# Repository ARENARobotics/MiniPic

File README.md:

# MiniPic: Benchtop Vacuum Tweezers

[-008000?style=for-the-badge&logo=shopify&logoColor=white)](https://arenarobotics.store/products/minipic?variant=54529778090197&utm_source=github&utm_medium=readme&utm_campaign=minipic_repo&utm_content=assembled_badge)
[-0000FF?style=for-the-badge&logo=shopify&logoColor=white)](https://arenarobotics.store/products/minipic?variant=54529778122965&utm_source=github&utm_medium=readme&utm_campaign=minipic_repo&utm_content=kit_badge)

Open-source vacuum tweezers built for repairability. Engineered for SMD soldering and precision rework, with a robust design adaptable to any application requiring controlled suction and handling of small parts.

---

### Features

* **Two operating modes:** foot pedal starts or stops the vacuum motor
* **Solenoid valve** for instant component release
* **Heat-resistant pen** rated up to **160°C**
* **Full set of precision needles and suction cups** for all sizes of SMD components
* Handles components down to **0201 (0.6 x 0.3mm)** and up to **100g**
* **Flexible silicone** vacuum tubing
* **MX hot-swap mechanical switch** in the foot pedal
* **Slip-resistant** rubber feet
* **Inline filter** to protect the vacuum motor
* **LED status indicator** for vacuum engagement

---

### Documentation & Source Files

* **[Assembly Manual](./docs/ASSEMBLY_MANUAL.pdf)** - Step-by-step kit assembly Instructions & quickstart guide
* **[BOM](./BOM.csv)** - Bill of materials including reference links for purchase
* **[Electronics Source](./electronics)** - KiCAD projects for PCBs
* **[CAD Exports](./cad/exports)** - CAD export files (step)
* **[CAD Source](./cad/source%20files)** - CAD source files (FreeCAD)

---

### Our Story

Last summer, we founded a company developing advanced electronics for robot combat competitions. We were inexperienced and didn’t understand the market so the project didn’t work out. Throughout the project, we spent a lot of time designing and assembling PCBs on a tight budget. Like many others, we found that tweezers were cumbersome tools for placing SMD components. The search for a better alternative led us to vacuum tweezers, tools designed to pick and place SMD components using controlled suction. The plan was to buy something off the shelf, but all of the products that were in our price range were not usable. On the other hand, the existing professional tools would have drained our bank account. We were stuck between cheap, low quality options and expensive industrial tools, most of which lacked all the features we were actually looking for.

Out of this frustration, one of our team members got to work, and in a few days, we had a functional tool that made assembly faster and easier than before. After using it ourselves, we realized we could provide a better alternative to others facing the same lack of options. Using our prototype as inspiration, we redesigned our vacuum tweezers from the ground up. Highly functional while still remaining simple and repairable.

See MiniPic in action at: [arenarobotics.store](https://arenarobotics.store?utm_source=github&utm_medium=readme&utm_campaign=minipic_repo&utm_content=story_link).

---

### Licensing

* **Hardware & CAD files (`/electronics`, `/cad`):** Licensed under [CERN-OHL-S-v2](LICENSE.md).
* **Documentation & Media (`/docs`):** Licensed under [CC BY-NC-ND 4.0](https://creativecommons.org/licenses/by-nc-nd/4.0/).
* **Branding & Trademarks:** "MiniPic" and "ARENA Robotics" are trademarks of ARENA Robotics LLC. All rights reserved.

--- 

*Designed & Built by ARENA Robotics.*

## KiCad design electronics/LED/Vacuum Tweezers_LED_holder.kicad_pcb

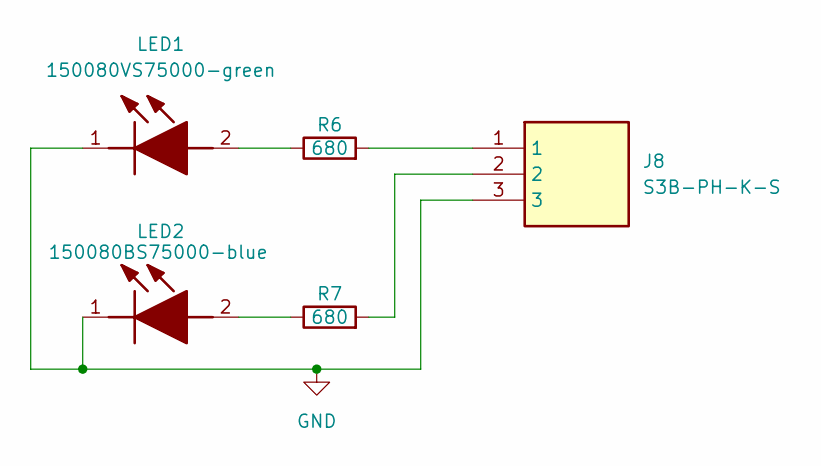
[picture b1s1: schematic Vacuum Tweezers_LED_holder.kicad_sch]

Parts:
J8: S3B-PH-K-S; S3BPHKS; Manufacturer_Part_Number S3B-PH-K-S
LED1: 150080VS75000-green; LEDC2012X70N; Manufacturer_Part_Number 150080VS75000; Mouser Part Number 710-150080VS75000
LED2: 150080BS75000-blue; LEDC2012X70N; Manufacturer_Part_Number 150080BS75000; Mouser Part Number 710-150080BS75000
R6, R7: 680; R_0805_2012Metric

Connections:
GND: J8.3, LED1.1 (K), LED2.1 (K)
unnamed: J8.1, R6.2
unnamed: J8.2, R7.2
unnamed: LED1.2 (A), R6.1
unnamed: LED2.2 (A), R7.1

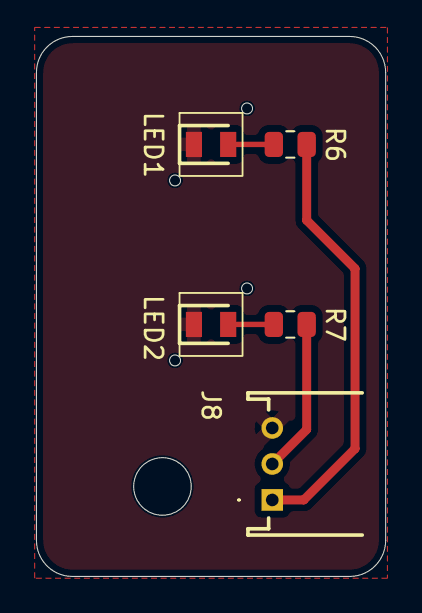
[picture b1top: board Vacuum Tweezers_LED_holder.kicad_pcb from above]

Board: 2 copper layers, 19.4 x 30.0 mm, 5 parts (0 on the bottom side), 5 nets.

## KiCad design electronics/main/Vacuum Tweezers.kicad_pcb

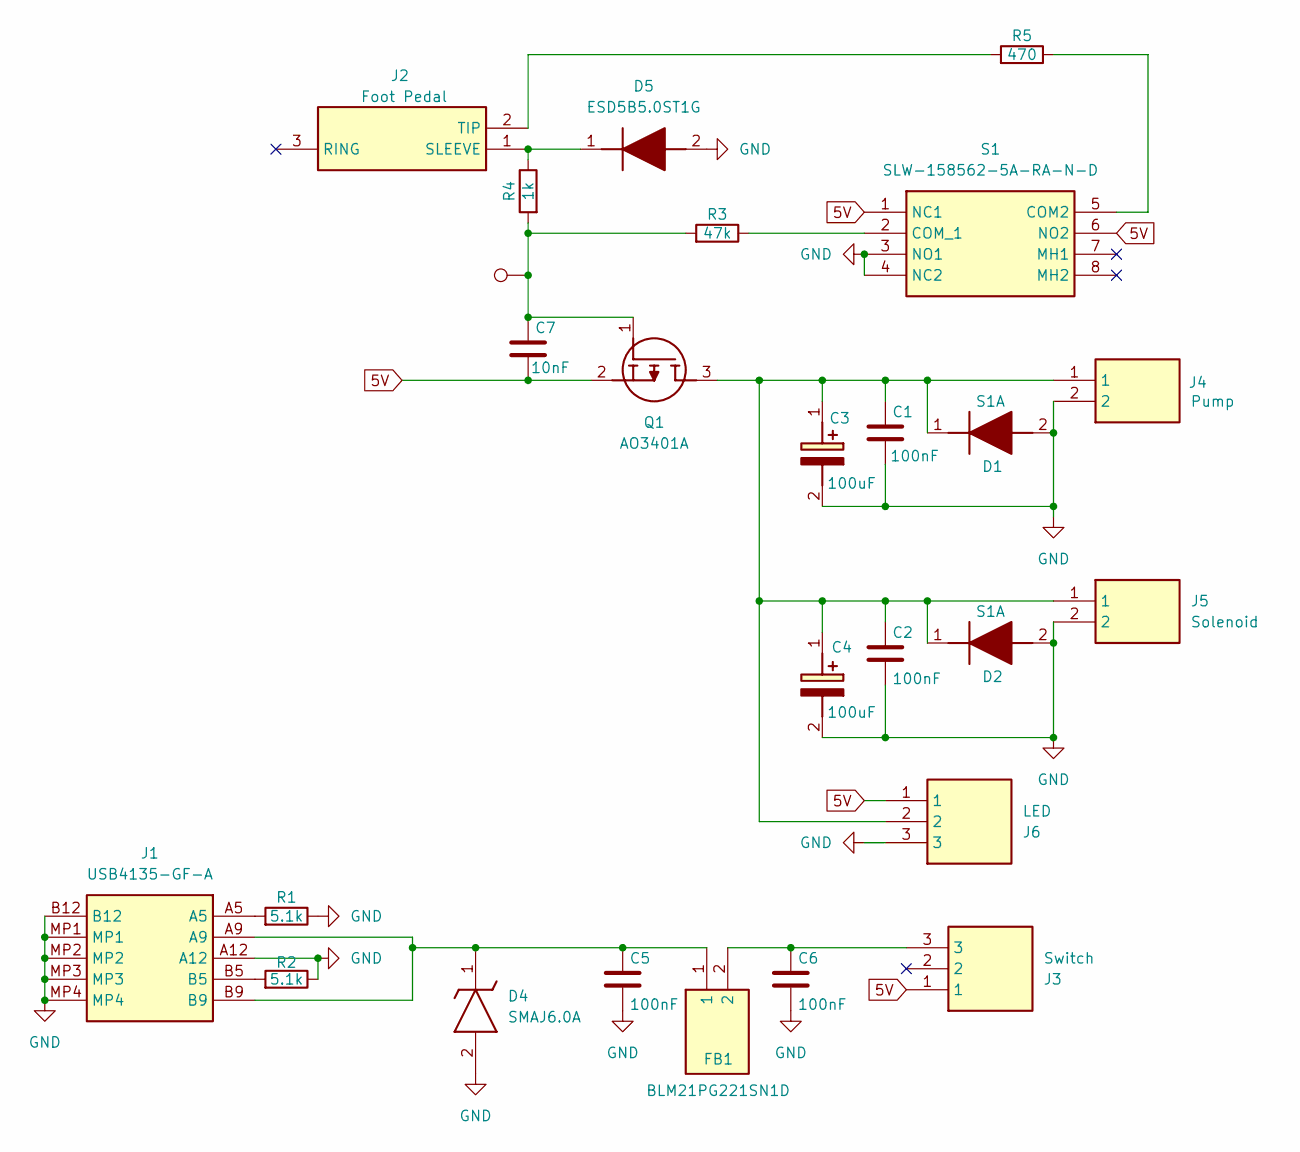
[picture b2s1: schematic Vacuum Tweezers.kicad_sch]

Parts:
C1, C2, C5, C6: 100nF; C_0805_2012Metric
C3, C4: 100uF; 865080343009; Manufacturer_Part_Number 865080343009; Mouser Part Number 710-865080343009
C7: 10nF; C_0805_2012Metric
D1, D2: S1A; DIOM5127X261N; Manufacturer_Part_Number S1A
D4: SMAJ6.0A; DIOM6626X229N; Manufacturer_Part_Number SMAJ6.0A; Mouser Part Number 576-SMAJ6.0A
D5: ESD5B5.0ST1G; SODFL1608X70N; Manufacturer_Part_Number ESD5B5.0ST1G; Mouser Part Number 863-ESD5B50ST1G
FB1: BLM21PG221SN1D; BEADC2012X105N; Manufacturer_Part_Number BLM21PG221SN1D; Mouser Part Number 81-BLM21P221SG
J1: USB4135-GF-A; USB4135GFA; Manufacturer_Part_Number USB4135-GF-A; Mouser Part Number 640-USB4135-GF-A
J2: Foot Pedal; SJ3523SMTTR; Manufacturer_Part_Number SJ-3523-SMT-TR; Mouser Part Number 490-SJ-3523-SMT-TR
J3: Switch; B3BXHALFSN; Manufacturer_Part_Number B3B-XH-A(LF)(SN); Mouser Part Number 306-B3BXHALFSNP
J4: Pump; B2BPHKS; Manufacturer_Part_Number B2B-PH-K-S
J5: Solenoid; B2BXHAGU; Manufacturer_Part_Number B2B-XH-A-GU; Mouser Part Number N/A
J6: LED; B3BPHKLLFSN; Manufacturer_Part_Number B3B-PH-KL (LF)(SN)
Q1: AO3401A; SOT95P280X125-3N; Manufacturer_Part_Number AO3401A
R1, R2: 5.1k; R_0805_2012Metric
R3: 47k; R_0805_2012Metric
R4: 1k; R_0805_2012Metric
R5: 470; R_0805_2012Metric
S1: SLW-158562-5A-RA-N-D; SW_SLW-158562-5A-RA-N-D; Manufacturer_Part_Number SLW-158562-5A-RA-N-D; Mouser Part Number 179-SLW1585625ARAND
TP1: TestPoint; TestPoint_Keystone_5000-5004_Miniature

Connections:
5V: C7.2, J3.1, J6.1, Q1.2 (S), S1.1 (NC1), S1.6 (NO2)
GND: C1.2, C2.2, C3.2 (-), C4.2 (-), C5.2, C6.2, D1.2 (A), D2.2 (A), D4.2 (A), D5.2 (A), J1.A12, J1.B12, J1.MP1, J1.MP2, J1.MP3, J1.MP4, J4.2, J5.2, J6.3, R1.1, R2.1, S1.3 (NO1), S1.4 (NC2)
unnamed: C1.1, C2.1, C3.1 (+), C4.1 (+), D1.1 (K), D2.1 (K), J4.1, J5.1, J6.2, Q1.3 (D)
unnamed: C6.1, FB1.2, J3.3
unnamed: C5.1, D4.1 (K), FB1.1, J1.A9, J1.B9
unnamed: D5.1 (K), J2.1 (SLEEVE), R4.2
unnamed: J1.A5, R1.2
unnamed: J1.B5, R2.2
unnamed: J2.2 (TIP), R5.1
unnamed: C7.1, Q1.1 (G), R3.1, R4.1, TP1.1 (1_1)
unnamed: R5.2, S1.5 (COM2)
unnamed: R3.2, S1.2 (COM_1)

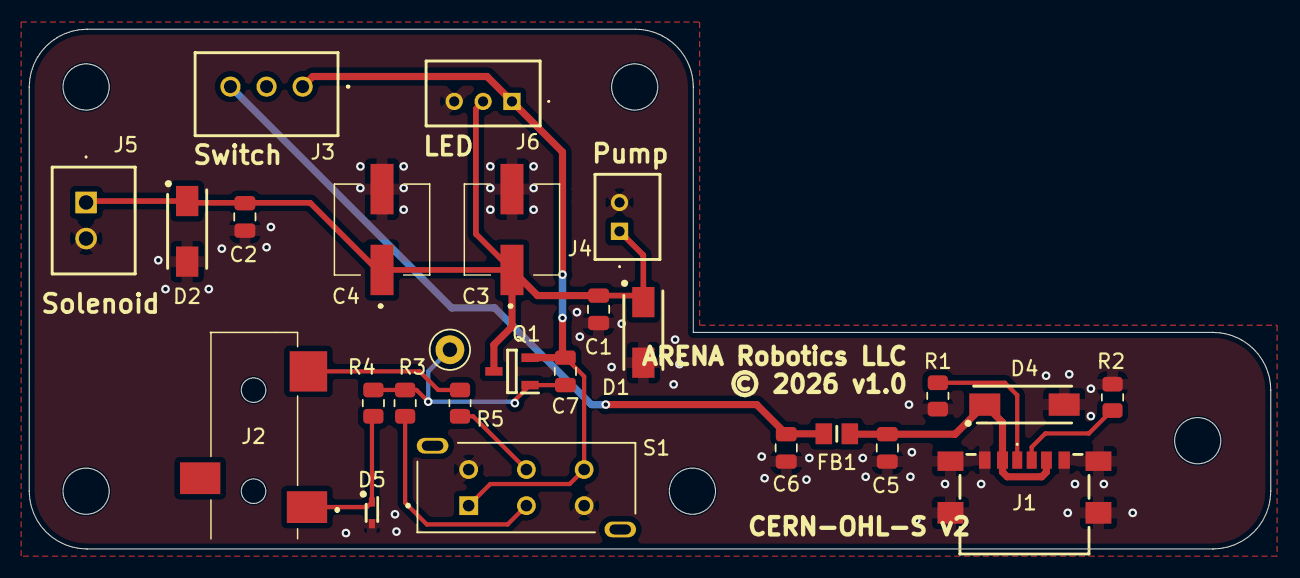
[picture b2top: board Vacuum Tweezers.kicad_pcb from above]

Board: 2 copper layers, 86.0 x 36.0 mm, 26 parts (0 on the bottom side), 12 nets.

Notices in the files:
electronics/main/Vacuum Tweezers.kicad_pcb:
© 2026 v1.0
